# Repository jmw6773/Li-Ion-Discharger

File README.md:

# Li-Ion-Discharger
Arduino discharger for Li-Ion batteries with selectable stop voltage and fan speed.

Original Design and Code by Adam Welch
* http://AdamWelch.Uk
* YouTube Video: https://www.youtube.com/embed/qtws6VSIoYk

Modified and extended features added by Jonathan Wells

##Features
- Able to discharge 4 18650 batteries simultaneously 
- Setup menu when battery is inserted to select the target discharge voltage.  
- Status LEDs for each battery (passively controlled by Mosfet gate signal) 
- Status monitoring and data transmission through bluetooth 
- Max current is at full charge and determined by the load resistors
  * I’m using 10W 8ohm resistors, so my max current is 525mA. This decreases as the battery discharges 
- Fan pin allows PWM switching a Mosfet to drive a small fan to cool the load resistors (heat sink highly recommended)
 * Be sure to have a fly-back diode on the fan

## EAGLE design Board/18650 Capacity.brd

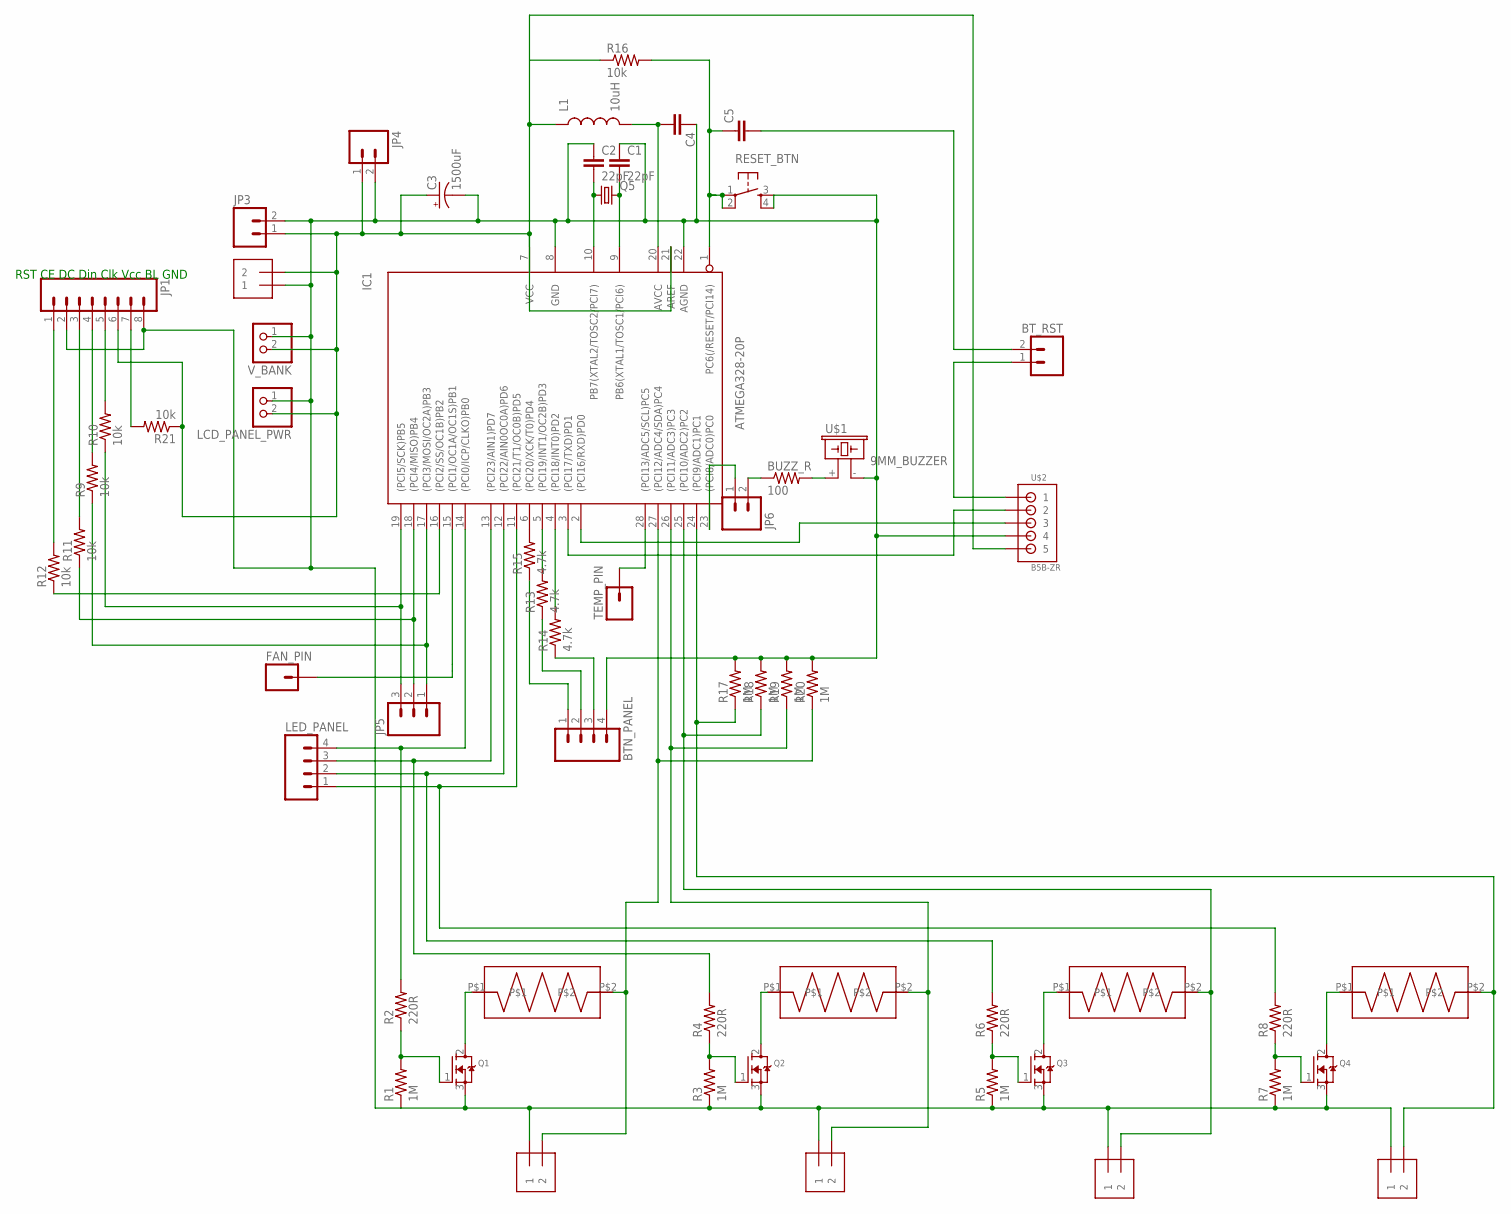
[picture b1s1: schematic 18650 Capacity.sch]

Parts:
5V_VIN: 1X2-3.5MM
BATT1, BATT2, BATT3, BATT4: 1X2-3.5MM
BTN_PANEL: M04LOCK; 1X04_LOCK
BT_RST: M02LOCK; 1X02_LOCK
BUZZ_R: 100; 1206
C1, C2: 22pF; CAP-PTH-SMALLEZ
C3: 1500uF; CPOL-RADIAL-100UF-25V
C4: CAPPTH1; CAP-PTH-5MM
C5: CAP_; AXIAL-5MM
FAN_PIN: M01PTH; 1X01
IC1: ATMEGA328-20P; DIL28-3
JP1: M08LOCK; 1X08_LOCK
JP3, JP4, JP6: M02LOCK; 1X02_LOCK
JP5: M03PTH; 1X03
L1: 10uH; RLB0912
LCD_PANEL_PWR: JST_2PIN-THM; JST-PH-2-THM
LED_PANEL: M04LOCK; 1X04_LOCK
LOAD4: CEMENT_RESISTOR
LOAD_1, LOAD_2: CEMENT_RESISTOR
Q1, Q2, Q3, Q4: MOSFET-NGDS_TO220V; TO220V
Q5: CRYTALHC49S; HC49/S
R1, R3, R5, R7: 1M; AXIAL-0.3
R2, R4, R6, R8: 220R; AXIAL-0.3
R9, R10, R11, R12, R16: 10k; AXIAL-0.3
R13, R14, R15: 4.7k; AXIAL-0.3
R17, R18, R19, R20: 1M; 0805
R21: 10k; 1206
RESET_BTN: TAC_SWITCHPTH; TACTILE-PTH
TEMP_PIN: M01PTH; 1X01
U$1: 9MM_BUZZER; AL11P
U$2: B5B-ZR
U$3: CEMENT_RESISTOR
V_BANK: JST_2PIN-THM; JST-PH-2-THM

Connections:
BATT_V1: BATT1.2, IC1.27 ((PCI12/ADC4/SDA)PC4), LOAD_1.P$2, R20.1
BATT_V2: BATT2.2, IC1.26 ((PCI11/ADC3)PC3), LOAD_2.P$2, R19.1
BATT_V3: BATT3.2, IC1.25 ((PCI10/ADC2)PC2), R18.1, U$3.P$2
BATT_V4: BATT4.2, IC1.24 ((PCI9/ADC1)PC1), LOAD4.P$2, R17.1
BT_RX: IC1.3 ((PCI17/TXD)PD1), U$2.2
BT_STATE: BT_RST.2, C5.P$2 (2)
BT_TX: IC1.2 ((PCI16/RXD)PD0), U$2.3
CLK: JP1.5, R10.P$2 (2)
CLK1: IC1.19 ((PCI5/SCK)PB5), JP5.3, R10.P$1 (1)
DC: JP1.3, R11.P$2 (2)
DC1: IC1.18 ((PCI4/MISO)PB4), JP5.2, R11.P$1 (1)
DIN: JP1.4, R9.P$2 (2)
DIN1: IC1.17 ((PCI3/MOSI/OC2A)PB3), JP5.1, R9.P$1 (1)
GATE1: IC1.14 ((PCI0/ICP/CLKO)PB0), LED_PANEL.4, R2.P$2 (2)
GATE2: IC1.13 ((PCI23/AIN1)PD7), LED_PANEL.3, R4.P$2 (2)
GATE3: IC1.12 ((PCI22/AIN0OC0A)PD6), LED_PANEL.2, R6.P$2 (2)
GATE4: IC1.11 ((PCI21/T1/OC0B)PD5), LED_PANEL.1, R8.P$2 (2)
GND: 5V_VIN.1, BATT1.1, BATT2.1, BATT3.1, BATT4.1, BTN_PANEL.4, C1.1, C2.1, C3.2 (-), C4.1, IC1.8 (GND), IC1.22 (AGND), JP1.2, JP1.8, JP3.2, JP4.2, LCD_PANEL_PWR.1 (2), Q1.3 (S), Q2.3 (S), Q3.3 (S), Q4.3 (S), R1.P$1 (1), R3.P$1 (1), R5.P$1 (1), R7.P$1 (1), R17.2, R18.2, R19.2, R20.2, RESET_BTN.3, RESET_BTN.4, U$1.- (2), U$2.4, V_BANK.1 (2)
unnamed: C2.2, IC1.10 (PB7(XTAL2/TOSC2/PCI7)), Q5.1
unnamed: LOAD4.P$1, Q4.2 (D)
unnamed: BUZZ_R.1, JP6.2
unnamed: IC1.4 ((PCI18/INT0)PD2), R14.P$2 (2)
unnamed: Q1.1 (G), R1.P$2 (2), R2.P$1 (1)
unnamed: Q2.1 (G), R3.P$2 (2), R4.P$1 (1)
unnamed: Q3.1 (G), R5.P$2 (2), R6.P$1 (1)
unnamed: Q4.1 (G), R7.P$2 (2), R8.P$1 (1)
unnamed: C1.2, IC1.9 (PB6(XTAL1/TOSC1/PCI6)), Q5.2
unnamed: C5.P$1 (1), IC1.1 (PC6(/RESET/PCI14)), R16.P$2 (2), RESET_BTN.1, RESET_BTN.2
unnamed: IC1.5 ((PCI19/INT1/OC2B)PD3), R13.P$2 (2)
unnamed: IC1.23 ((PCI8/ADC0)PC0), JP6.1
unnamed: C4.2, IC1.20 (AVCC), L1.2
unnamed: IC1.6 ((PCI20/XCK/T0)PD4), R15.P$2 (2)
unnamed: BTN_PANEL.2, R13.P$1 (1)
unnamed: LOAD_1.P$1, Q1.2 (D)
unnamed: LOAD_2.P$1, Q2.2 (D)
unnamed: Q3.2 (D), U$3.P$1
unnamed: BTN_PANEL.3, R14.P$1 (1)
unnamed: BTN_PANEL.1, R15.P$1 (1)
unnamed: BT_RST.1, U$2.1
unnamed: BUZZ_R.2, U$1.+ (1)
unnamed: IC1.28 ((PCI13/ADC5/SCL)PC5), TEMP_PIN.1
PMW_LED: JP1.7, R21.2
PWM_LED1: FAN_PIN.1, IC1.15 ((PCI1/OC1A/OC1S)PB1)
RST: JP1.1, R12.P$2 (2)
RST1: IC1.16 ((PCI2/SS/OC1B)PB2), R12.P$1 (1)
VCC: 5V_VIN.2, C3.1 (+), IC1.7 (VCC), IC1.21 (AREF), JP1.6, JP3.1, JP4.1, L1.1, LCD_PANEL_PWR.2 (1), R16.P$1 (1), R21.1, U$2.5, V_BANK.2 (1)

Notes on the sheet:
RST CE DC Din Clk Vcc BL GND

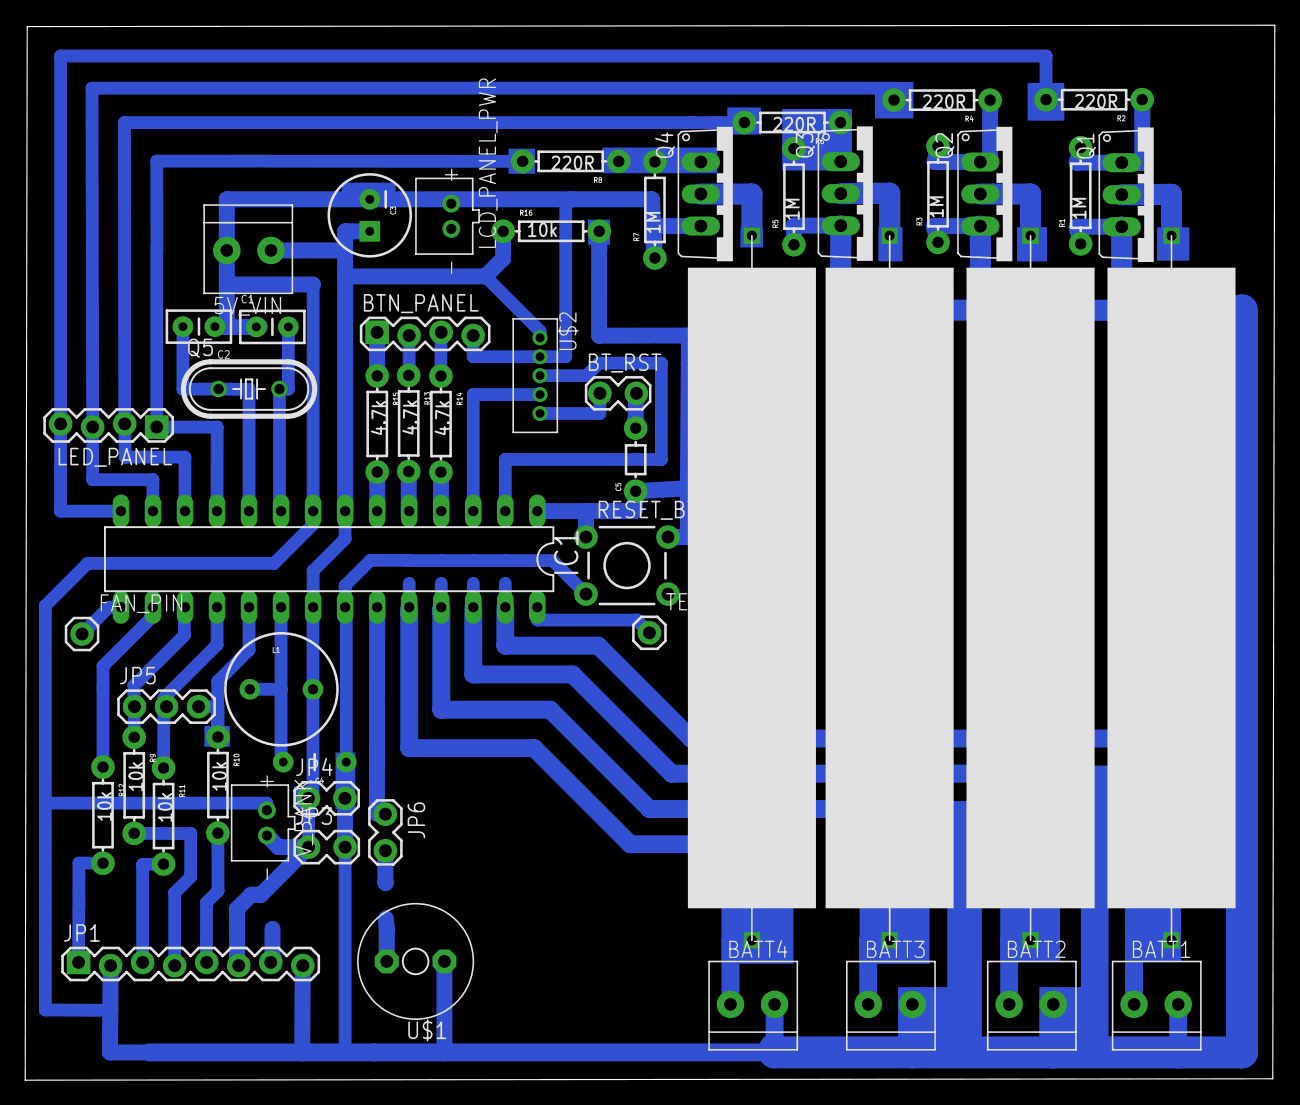
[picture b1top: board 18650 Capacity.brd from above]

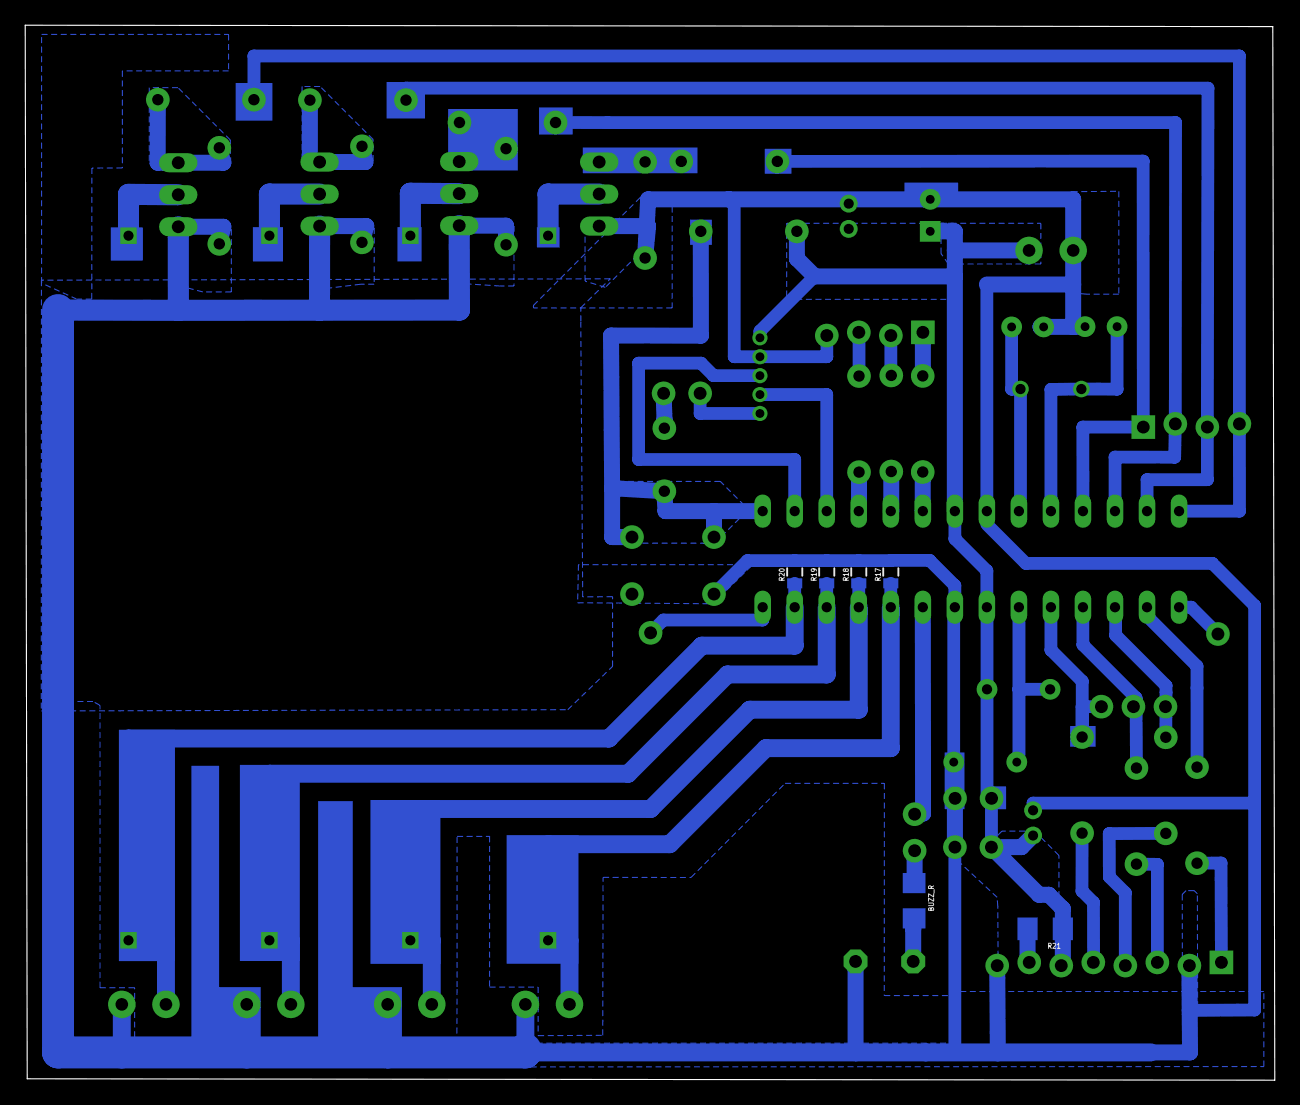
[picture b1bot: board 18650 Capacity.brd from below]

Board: 2 copper layers, 99.1 x 83.7 mm, 58 parts (6 on the bottom side), 46 nets.

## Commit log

2016-09-08 Created Arduino Folder
2016-09-08 Removed root file
2016-09-10 Added Eagle Files
2016-09-10 Oops'ed a file
2016-09-10 Readme update
2016-09-10 Readme
2016-09-10 Board Update
2016-09-10 Removed global numBatteries, replaced with local variable
2016-09-11 Added PNG images of the schematic and routed board.
2016-09-12 Photo of board
2019-03-13 Create test

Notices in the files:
parts and their libraries:
SparkFun-Connectors: Licensing: Creative Commons ShareAlike 4.0 International - https://creativecommons.org/licenses/by-sa/4.0
